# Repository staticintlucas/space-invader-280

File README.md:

# space-invader-280
PCB for Noxary 280 using NMB/Hi-Tek Series 725 "Space Invader" switches

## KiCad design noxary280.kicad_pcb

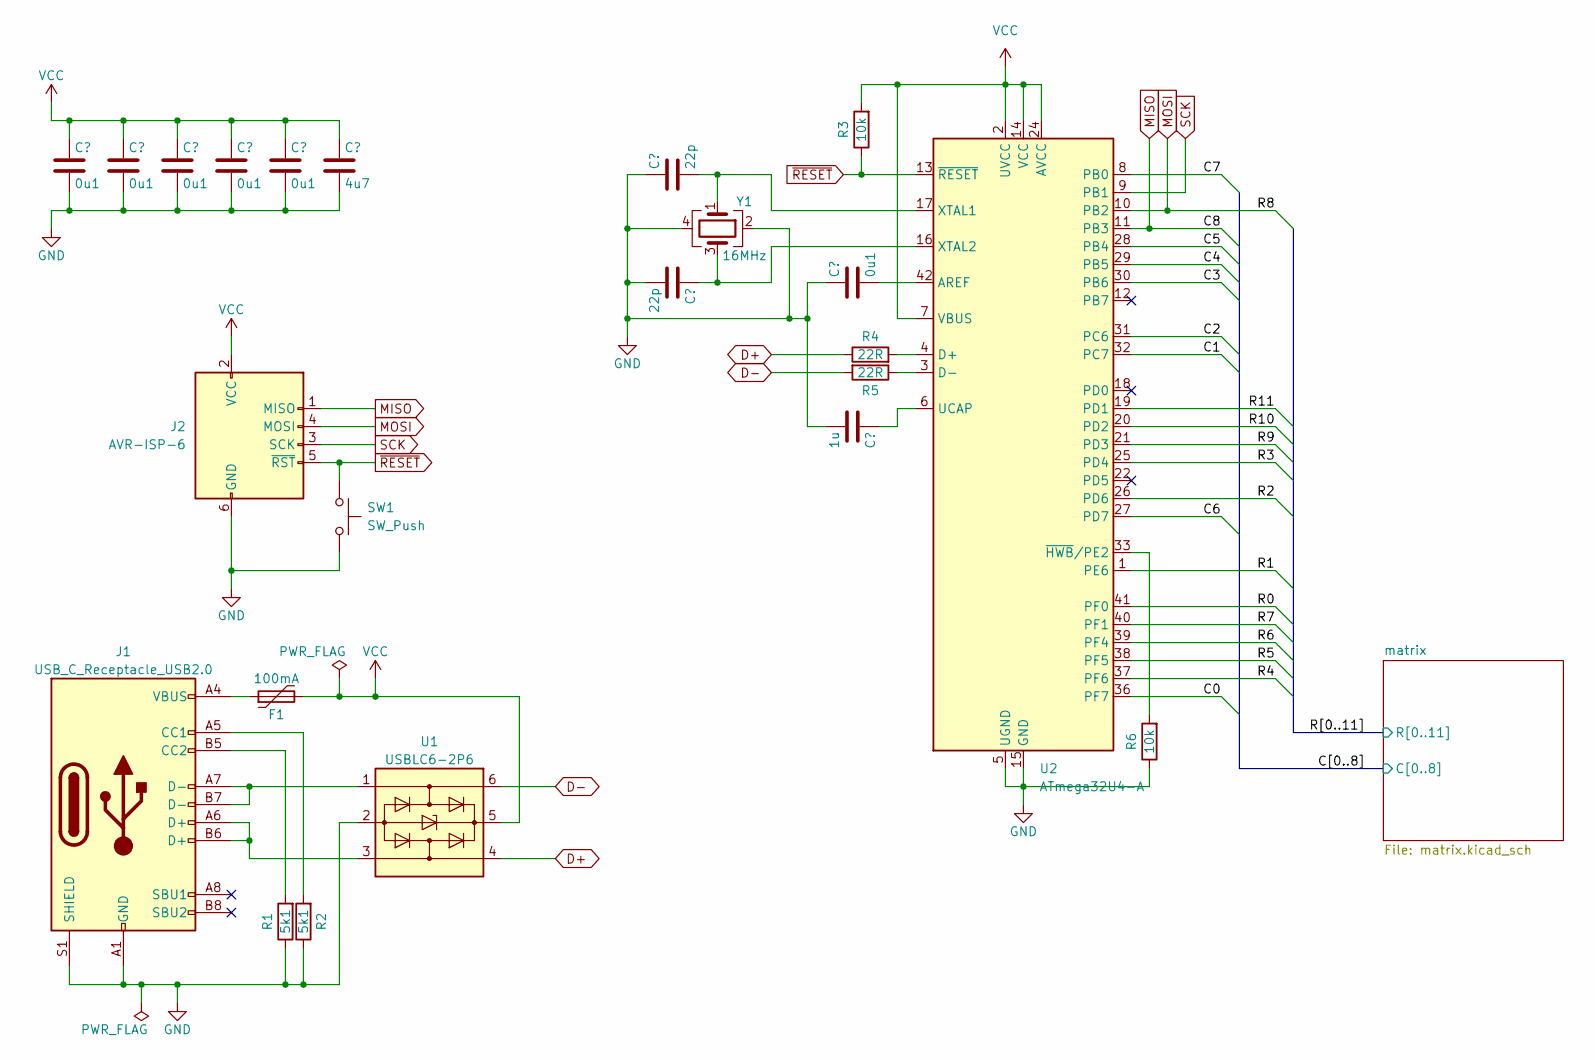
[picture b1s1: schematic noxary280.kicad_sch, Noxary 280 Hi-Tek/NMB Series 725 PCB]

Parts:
C1, C2, C3, C4, C5, C9: 0u1; C_0805_2012Metric
C6: 4u7; C_0805_2012Metric
C7, C8: 22p; C_0805_2012Metric
C10: 1u; C_0805_2012Metric
F1: 100mA; Fuse_0805_2012Metric
J1: USB_C_Receptacle_USB2.0; USB_C_Receptacle_HRO_TYPE-C-31-M-12
J2: AVR-ISP-6; PinHeader_2x03_P2.54mm_Vertical
R1, R2: 5k1; R_0805_2012Metric
R3, R6: 10k; R_0805_2012Metric
R4, R5: 22R; R_0805_2012Metric
SW1: SW_Push; SW_SPST_TL3342
U1: USBLC6-2P6; SOT-666
U2: ATmega32U4-A; TQFP-44_10x10mm_P0.8mm
Y1: 16MHz; Crystal_SMD_SeikoEpson_FA238-4Pin_3.2x2.5mm

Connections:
/C0: U2.36 (PF7); also elsewhere on the board
/C1: U2.32 (PC7); also elsewhere on the board
/C2: U2.31 (PC6); also elsewhere on the board
/C3: U2.30 (PB6); also elsewhere on the board
/C4: U2.29 (PB5); also elsewhere on the board
/C5: U2.28 (PB4); also elsewhere on the board
/C6: U2.27 (PD7); also elsewhere on the board
/C7: U2.8 (PB0); also elsewhere on the board
/R0: U2.41 (PF0); also elsewhere on the board
/R1: U2.1 (PE6); also elsewhere on the board
/R2: U2.26 (PD6); also elsewhere on the board
/R3: U2.25 (PD4); also elsewhere on the board
/R4: U2.37 (PF6); also elsewhere on the board
/R5: U2.38 (PF5); also elsewhere on the board
/R6: U2.39 (PF4); also elsewhere on the board
/R7: U2.40 (PF1); also elsewhere on the board
/R9: U2.21 (PD3); also elsewhere on the board
/R10: U2.20 (PD2); also elsewhere on the board
/R11: U2.19 (PD1); also elsewhere on the board
D+: R4.1, U1.4 (I/O2)
D-: R5.2, U1.6 (I/O1)
GND: C1.2, C2.2, C3.2, C4.2, C5.2, C6.2, C7.1, C8.2, C9.1, C10.2, J1.A1 (GND), J1.A12 (GND), J1.B1 (GND), J1.B12 (GND), J1.S1 (SHIELD), J2.6 (GND), R1.1, R2.1, R6.1, SW1.2, U1.2 (GND), U2.5 (UGND), U2.15 (GND), U2.23 (GND), U2.35 (GND), U2.43 (GND), Y1.2, Y1.4
MISO: J2.1 (MISO), U2.11 (PB3); also elsewhere on the board
MOSI: J2.4 (MOSI), U2.10 (PB2); also elsewhere on the board
unnamed: F1.1, J1.A4 (VBUS), J1.A9 (VBUS), J1.B4 (VBUS), J1.B9 (VBUS)
unnamed: J1.A5 (CC1), R2.2
unnamed: J1.B5 (CC2), R1.2
unnamed: J1.A6 (D+), J1.B6 (D+), U1.3 (I/O2)
unnamed: J1.A7 (D-), J1.B7 (D-), U1.1 (I/O1)
unnamed: C9.2, U2.42 (AREF)
unnamed: R4.2, U2.4 (D+)
unnamed: R5.1, U2.3 (D-)
unnamed: C10.1, U2.6 (UCAP)
unnamed: C7.2, U2.17 (XTAL1), Y1.1
unnamed: C8.1, U2.16 (XTAL2), Y1.3
unnamed: R6.2, U2.33 (~HWB/PE2)
SCK: J2.3 (SCK), U2.9 (PB1)
VCC: C1.1, C2.1, C3.1, C4.1, C5.1, C6.1, F1.2, J2.2 (VCC), R3.2, U1.5 (VBUS), U2.2 (UVCC), U2.7 (VBUS), U2.14 (VCC), U2.24 (AVCC), U2.34 (VCC), U2.44 (AVCC)
~RESET: J2.5 (~RST), R3.1, SW1.1, U2.13 (~RESET)

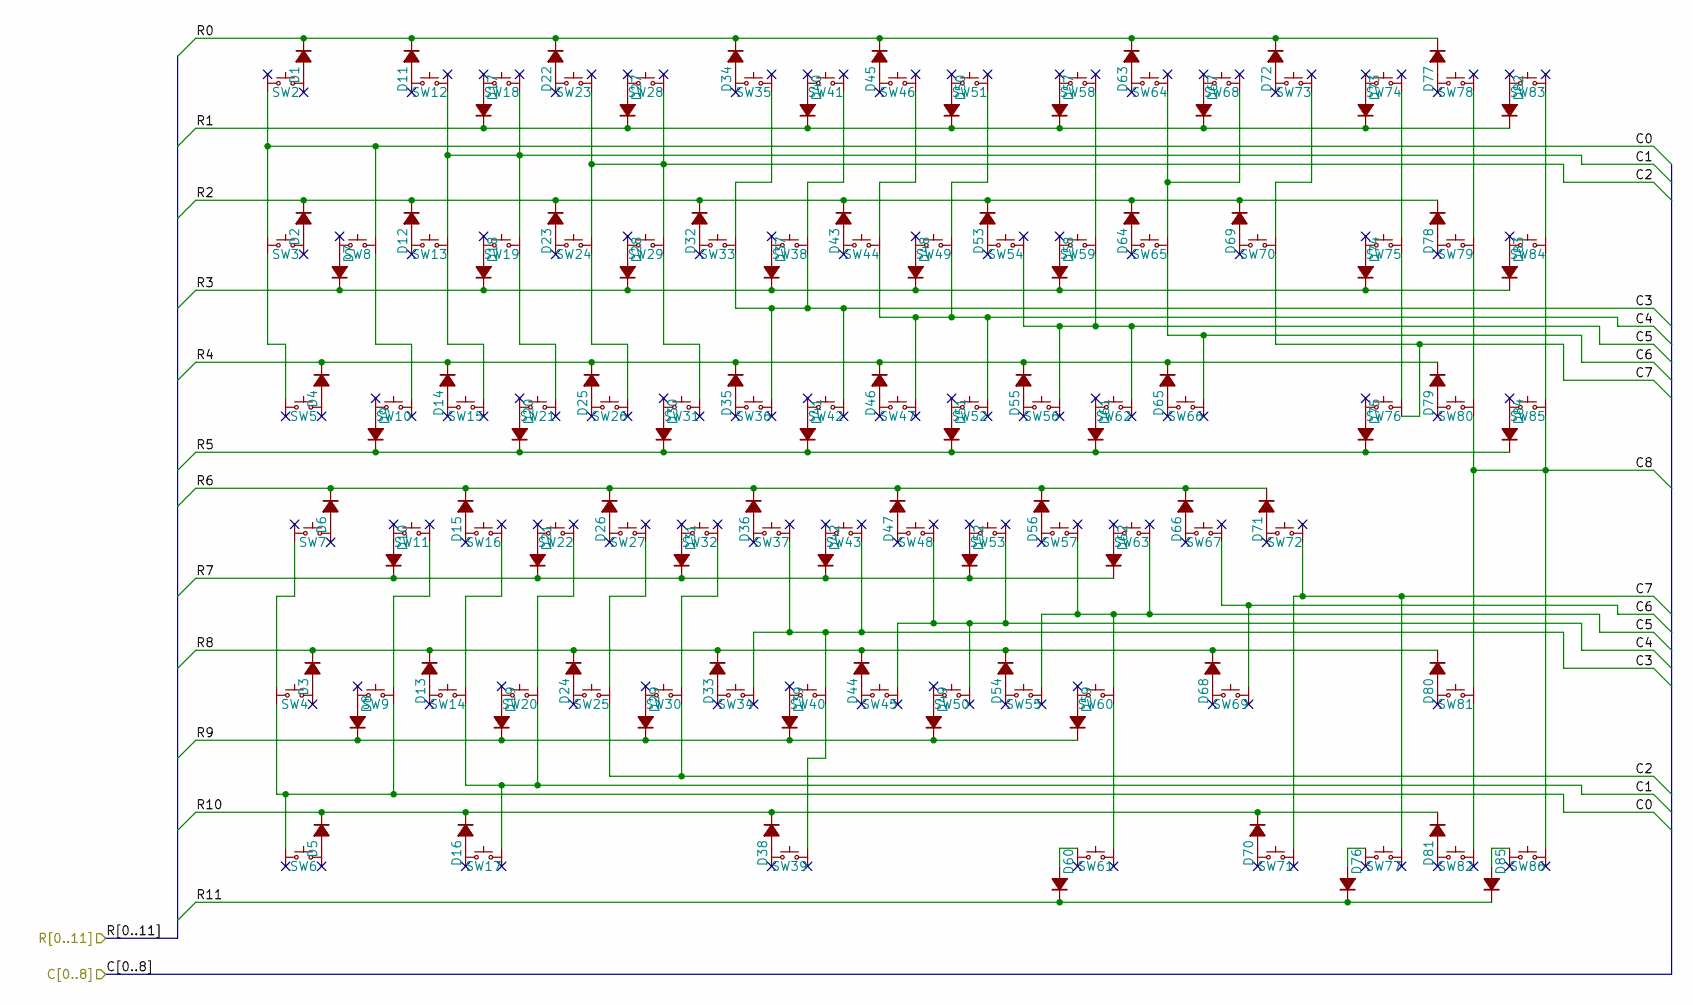
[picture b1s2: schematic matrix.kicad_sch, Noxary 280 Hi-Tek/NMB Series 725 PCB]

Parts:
D1, D2, D3, D4, D5, D6, D7, D8, D9, D10, D11, D12, D13, D14, D15, D16, D17, D18, D19, D20, D21, D22, D23, D24, D25, D26, D27, D28, D29, D30, D31, D32, D33, D34, D35, D36, D37, D38, D39, D40, D41, D42, D43, D44, D45, D46, D47, D48, D49, D50, D51, D52, D53, D54, D55, D56, D57, D58, D59, D60, D61, D62, D63, D64, D65, D66, D67, D68, D69, D70, D71, D72, D73, D74, D75, D76, D77, D78, D79, D80, D81, D82, D83, D84, D85: D_Small_Filled; D_SOD-123
SW2, SW3, SW4, SW5, SW6, SW7, SW8, SW9, SW10, SW11, SW12, SW13, SW14, SW15, SW16, SW17, SW18, SW19, SW20, SW21, SW22, SW23, SW24, SW25, SW26, SW27, SW28, SW29, SW30, SW31, SW32, SW33, SW34, SW35, SW36, SW37, SW38, SW39, SW40, SW41, SW42, SW43, SW44, SW45, SW46, SW47, SW48, SW49, SW50, SW51, SW52, SW53, SW54, SW55, SW56, SW57, SW58, SW59, SW60, SW61, SW62, SW63, SW64, SW65, SW66, SW67, SW68, SW69, SW70, SW71, SW72, SW73, SW74, SW75, SW76, SW77, SW78, SW79, SW80, SW81, SW82, SW83, SW84, SW85, SW86: SW_Push_4_Pin; SW_HiTek_725

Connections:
/C0: SW2.3 (1), SW3.1, SW4.3 (1), SW6.1, SW8.2, SW9.4 (2); also elsewhere on the board
/C1: SW12.4 (2), SW13.2, SW14.4 (2), SW17.2, SW18.4 (2), SW19.2, SW20.4 (2); also elsewhere on the board
/C2: SW23.4 (2), SW24.2, SW25.4 (2), SW28.4 (2), SW29.2, SW30.4 (2); also elsewhere on the board
/C3: SW33.4 (2), SW34.2, SW36.2, SW37.4 (2), SW38.4 (2), SW40.2, SW42.2, SW43.4 (2); also elsewhere on the board
/C4: SW44.4 (2), SW45.2, SW47.2, SW48.4 (2), SW49.4 (2), SW50.2, SW52.2, SW53.4 (2); also elsewhere on the board
/C5: SW54.4 (2), SW55.2, SW56.2, SW57.4 (2), SW59.4 (2), SW60.2, SW62.2, SW63.4 (2); also elsewhere on the board
/C6: SW65.4 (2), SW66.2, SW67.4 (2), SW69.2; also elsewhere on the board
/C7: SW70.4 (2), SW71.2, SW72.4 (2), SW76.4 (2), SW77.2; also elsewhere on the board
/R0: D1.1 (K), D11.1 (K), D22.1 (K), D34.1 (K), D45.1 (K), D63.1 (K), D72.1 (K), D77.1 (K); also elsewhere on the board
/R1: D17.1 (K), D27.1 (K), D40.1 (K), D50.1 (K), D57.1 (K), D67.1 (K), D73.1 (K), D82.1 (K); also elsewhere on the board
/R2: D2.1 (K), D12.1 (K), D23.1 (K), D32.1 (K), D43.1 (K), D53.1 (K), D64.1 (K), D69.1 (K), D78.1 (K); also elsewhere on the board
/R3: D7.1 (K), D18.1 (K), D28.1 (K), D37.1 (K), D48.1 (K), D58.1 (K), D74.1 (K), D83.1 (K); also elsewhere on the board
/R4: D4.1 (K), D14.1 (K), D25.1 (K), D35.1 (K), D46.1 (K), D55.1 (K), D65.1 (K), D79.1 (K); also elsewhere on the board
/R5: D9.1 (K), D20.1 (K), D30.1 (K), D41.1 (K), D51.1 (K), D61.1 (K), D75.1 (K), D84.1 (K); also elsewhere on the board
/R6: D6.1 (K), D15.1 (K), D26.1 (K), D36.1 (K), D47.1 (K), D56.1 (K), D66.1 (K), D71.1 (K); also elsewhere on the board
/R7: D10.1 (K), D21.1 (K), D31.1 (K), D42.1 (K), D52.1 (K), D62.1 (K); also elsewhere on the board
/R9: D8.1 (K), D19.1 (K), D29.1 (K), D39.1 (K), D49.1 (K), D59.1 (K); also elsewhere on the board
/R10: D5.1 (K), D16.1 (K), D38.1 (K), D70.1 (K), D81.1 (K); also elsewhere on the board
/R11: D60.1 (K), D76.1 (K), D85.1 (K); also elsewhere on the board
MISO: SW80.4 (2), SW81.2, SW85.4 (2), SW86.2; also elsewhere on the board
MOSI: D3.1 (K), D13.1 (K), D24.1 (K), D33.1 (K), D44.1 (K), D54.1 (K), D68.1 (K), D80.1 (K); also elsewhere on the board
unnamed: D1.2 (A), SW2.2
unnamed: D2.2 (A), SW3.2
unnamed: D3.2 (A), SW4.2
unnamed: D4.2 (A), SW5.2
unnamed: D5.2 (A), SW6.2
unnamed: D6.2 (A), SW7.2
unnamed: D7.2 (A), SW8.3 (1)
unnamed: D8.2 (A), SW9.3 (1)
unnamed: D9.2 (A), SW10.3 (1)
unnamed: D10.2 (A), SW11.3 (1)
unnamed: D11.2 (A), SW12.1
unnamed: D12.2 (A), SW13.1
unnamed: D13.2 (A), SW14.1
unnamed: D14.2 (A), SW15.1
unnamed: D15.2 (A), SW16.1
unnamed: D16.2 (A), SW17.1
unnamed: D17.2 (A), SW18.3 (1)
unnamed: D18.2 (A), SW19.3 (1)
unnamed: D19.2 (A), SW20.3 (1)
unnamed: D20.2 (A), SW21.3 (1)
unnamed: D21.2 (A), SW22.3 (1)
unnamed: D22.2 (A), SW23.1
unnamed: D23.2 (A), SW24.1
unnamed: D24.2 (A), SW25.1
unnamed: D25.2 (A), SW26.1
unnamed: D26.2 (A), SW27.1
unnamed: D27.2 (A), SW28.3 (1)
unnamed: D28.2 (A), SW29.3 (1)
unnamed: D29.2 (A), SW30.3 (1)
unnamed: D30.2 (A), SW31.3 (1)
unnamed: D31.2 (A), SW32.3 (1)
unnamed: D32.2 (A), SW33.1
unnamed: D33.2 (A), SW34.1
unnamed: D34.2 (A), SW35.1
unnamed: D35.2 (A), SW36.1
unnamed: D36.2 (A), SW37.1
unnamed: D37.2 (A), SW38.3 (1)
unnamed: D38.2 (A), SW39.1
unnamed: D39.2 (A), SW40.3 (1)
unnamed: D40.2 (A), SW41.3 (1)
unnamed: D41.2 (A), SW42.3 (1)
unnamed: D42.2 (A), SW43.3 (1)
unnamed: D43.2 (A), SW44.1
unnamed: D44.2 (A), SW45.1
unnamed: D45.2 (A), SW46.1
unnamed: D46.2 (A), SW47.1
unnamed: D47.2 (A), SW48.1
unnamed: D48.2 (A), SW49.3 (1)
unnamed: D49.2 (A), SW50.3 (1)
unnamed: D50.2 (A), SW51.3 (1)
unnamed: D51.2 (A), SW52.3 (1)
unnamed: D52.2 (A), SW53.3 (1)
unnamed: D53.2 (A), SW54.1
unnamed: D54.2 (A), SW55.1
unnamed: D55.2 (A), SW56.1
unnamed: D56.2 (A), SW57.1
unnamed: D57.2 (A), SW58.3 (1)
unnamed: D58.2 (A), SW59.3 (1)
unnamed: D59.2 (A), SW60.3 (1)
unnamed: D60.2 (A), SW61.1
unnamed: D61.2 (A), SW62.3 (1)
unnamed: D62.2 (A), SW63.3 (1)
unnamed: D63.2 (A), SW64.1
unnamed: D64.2 (A), SW65.1
unnamed: D65.2 (A), SW66.1
unnamed: D66.2 (A), SW67.1
unnamed: D67.2 (A), SW68.3 (1)
unnamed: D68.2 (A), SW69.1
unnamed: D69.2 (A), SW70.1
unnamed: D70.2 (A), SW71.1
unnamed: D71.2 (A), SW72.1
unnamed: D72.2 (A), SW73.1
unnamed: D73.2 (A), SW74.3 (1)
unnamed: D74.2 (A), SW75.3 (1)
unnamed: D75.2 (A), SW76.3 (1)
unnamed: D76.2 (A), SW77.1
unnamed: D77.2 (A), SW78.1
unnamed: D78.2 (A), SW79.1
unnamed: D79.2 (A), SW80.1
unnamed: D80.2 (A), SW81.1
unnamed: D81.2 (A), SW82.1
unnamed: D82.2 (A), SW83.3 (1)
unnamed: D83.2 (A), SW84.3 (1)
unnamed: D84.2 (A), SW85.3 (1)
unnamed: D85.2 (A), SW86.1
unnamed: SW3.3 (1), SW5.1
unnamed: SW4.1, SW7.3 (1)
unnamed: SW8.4 (2), SW10.2
unnamed: SW9.2, SW11.4 (2)
unnamed: SW13.4 (2), SW15.2
unnamed: SW14.2, SW16.4 (2)
unnamed: SW19.4 (2), SW21.2
unnamed: SW20.2, SW22.4 (2)
unnamed: SW24.4 (2), SW26.2
unnamed: SW25.2, SW27.4 (2)
unnamed: SW29.4 (2), SW31.2
unnamed: SW30.2, SW32.4 (2)
unnamed: SW33.2, SW35.4 (2)
unnamed: SW38.2, SW41.4 (2)
unnamed: SW39.2, SW40.4 (2)
unnamed: SW44.2, SW46.4 (2)
unnamed: SW49.2, SW51.4 (2)
unnamed: SW58.4 (2), SW59.2
unnamed: SW60.4 (2), SW61.2
unnamed: SW64.4 (2), SW65.2, SW68.4 (2)
unnamed: SW70.2, SW73.4 (2)
unnamed: SW74.4 (2), SW75.2
unnamed: SW75.4 (2), SW76.2
unnamed: SW78.4 (2), SW79.2
unnamed: SW79.4 (2), SW80.2
unnamed: SW81.4 (2), SW82.2
unnamed: SW83.4 (2), SW84.2
unnamed: SW84.4 (2), SW85.2

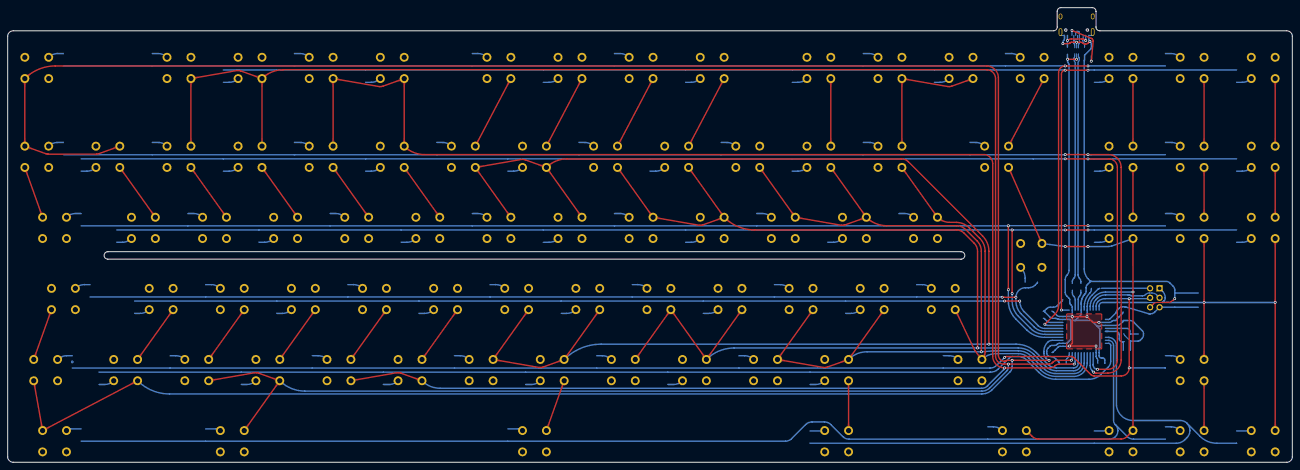
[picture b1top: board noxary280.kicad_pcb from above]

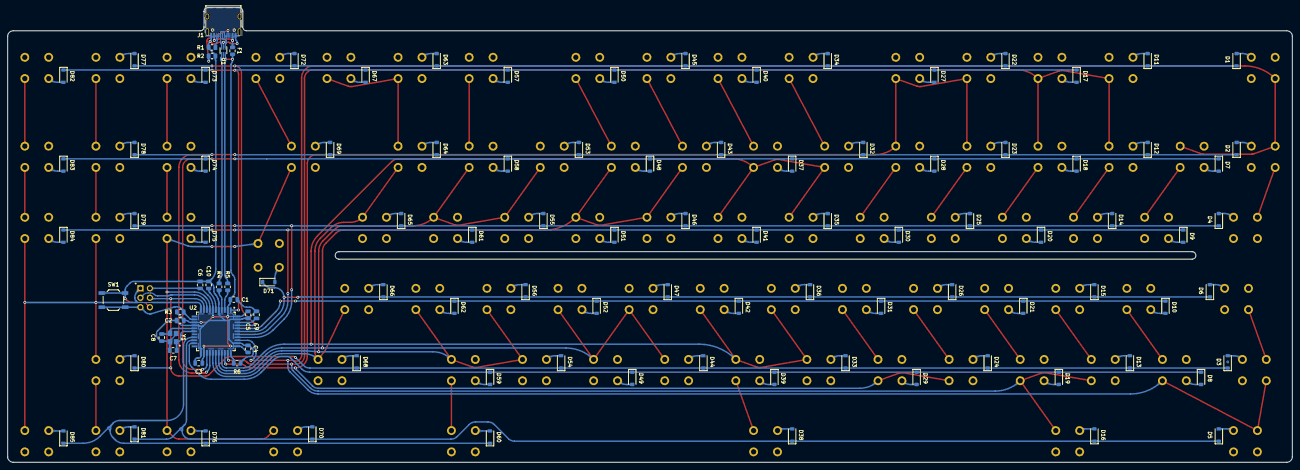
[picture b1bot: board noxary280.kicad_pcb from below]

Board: 2 copper layers, 344.2 x 121.8 mm, 193 parts (108 on the bottom side), 152 nets.

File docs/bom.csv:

Value,Designator,Footprint
0u1,"C1, C2, C3, C4, C5, C9",805
4u7,C6,805
22p,"C7, C8",805
1u,C10,805
1N4148W,"D1, D2, D3, D4, D5, D6, D7, D8, D9, D10, D11, D12, D13, D14, D15, D16, D17, D18, D19, D20, D21, D22, D23, D24, D25, D26, D27, D28, D29, D30, D31, D32, D33, D34, D35, D36, D37, D38, D39, D40, D41, D42, D43, D44, D45, D46, D47, D48, D49, D50, D51, D52, D53, D54, D55, D56, D57, D58, D59, D60, D61, D62, D63, D64, D65, D66, D67, D68, D69, D70, D71, D72, D73, D74, D75, D76, D77, D78, D79, D80, D81, D82, D83, D84, D85",SOD-123F
100mA,F1,805
HRO TYPE-C-31-M-12,J1,USB C Receptacle
5k1,"R1, R2",805
10k,"R3, R6",805
22R,"R4, R5",805
TL3342,SW1,TL3342
USBLC6-2P6,U1,SOT-666
ATmega32U4-A,U2,TQFP-44 10x10mm P0.8mm
16MHz,Y1,SeikoEpson FA238

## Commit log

2023-11-12 Add LICENCE
2023-11-12 Initial design
